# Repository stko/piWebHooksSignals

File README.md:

# piWebHooksSignals & PiPowerOff
## Introduction

This application do two things
- the hardware provides a complete power on/off system, where the raspi can be powered by a battery powerpack and turns himself off after finishing his job. In off state the battery is completely disconnected, so there's no quiescent current which could drain the battery.
 - the software deamon  manages the LEDs and the poweroff. It's controlled by ascii commands received on port 3000.

## Details
The hardware power on is triggered by a short press on the button. When the raspi is going into power off state at the end, it pulls GPIO pin 22 to HIGH, which switches the hardware power off again. (In case of emergency, a longer press also switches the power off)
The sample application reads the `webhooks.cfg` and tries to fire all found webhooks out of the config, while it send ASCII status commands via TCP port 3000 to the LED & power control task. At the end the command EXIT makes the system to power off.

## Install

To install piWebHooksSignals, get a virgin raspian lite image from raspberry.org (tested on raspian stretch)
boot the virgin raspian image, login
start the install script with

    bash <(curl -s https://raw.githubusercontent.com/stko/piWebHooksSignals/master/install.sh)

the installation will take appr. 20 minutes.

After the installation you should adjust your settings before reboot, because after that your file system will be read only (which you can temporarily change with `sudo mount -o remount,rw /` then)

In case of the sample application, the settings would be the UMTS stick settings in `/etc/wvdial.conf` and the web hooks to call in `/etc/piWebHooksSignals/webhooks.cfg`

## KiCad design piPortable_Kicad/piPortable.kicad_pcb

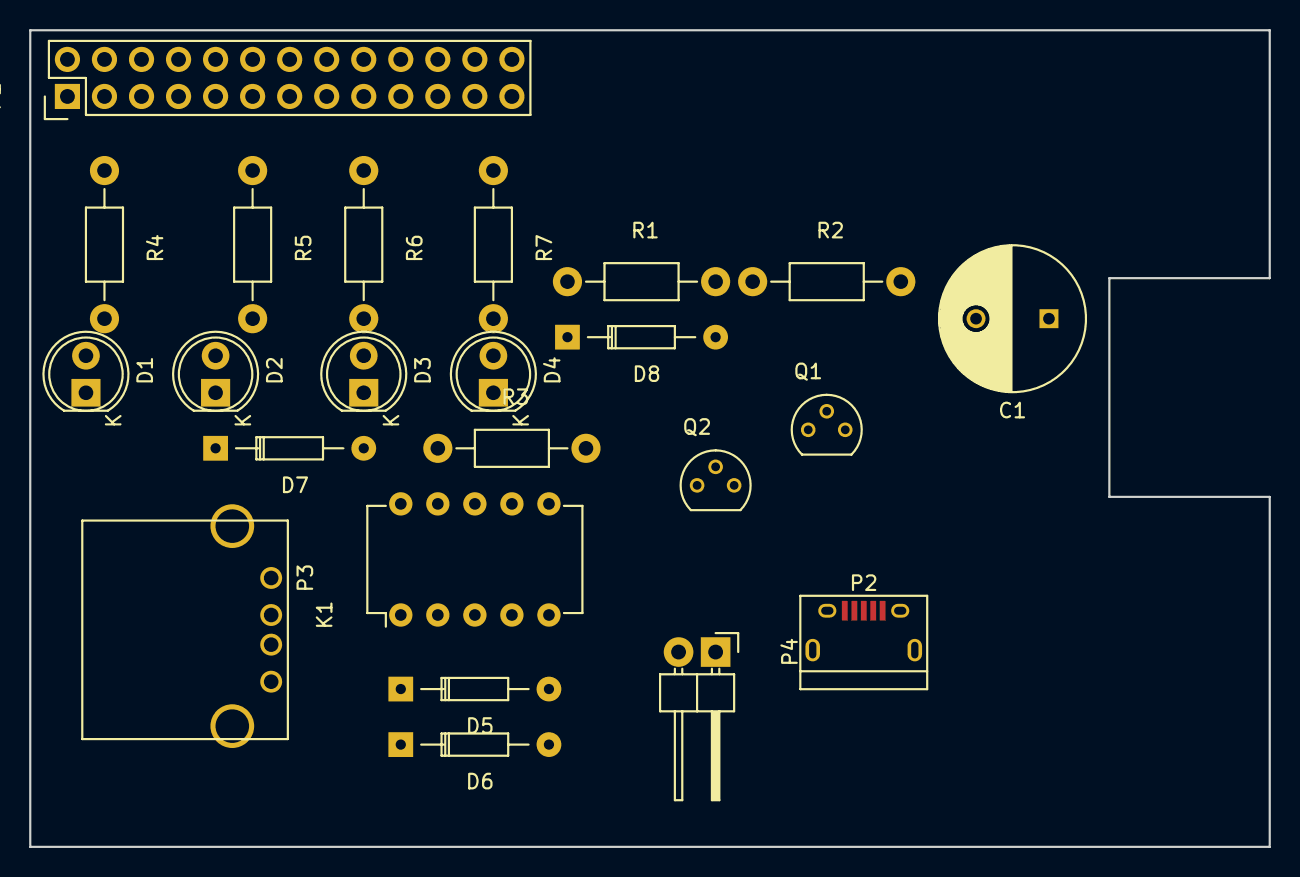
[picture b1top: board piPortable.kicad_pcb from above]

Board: 2 copper layers, 85.0 x 56.0 mm, 23 parts (0 on the bottom side), 17 nets, no tracks yet.

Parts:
C1: CP_Small; C_Radial_D10_L13_P5
D1: Power; LED-5MM
D2: Green; LED-5MM
D3: Yellow; LED-5MM
D4: Red; LED-5MM
D5, D6, D7, D8: D4148; Diode_DO-35_SOD27_Horizontal_RM10
K1: G6S-2; DIP-10_W7.62mm
P1: CONN_13X2; Pin_Header_Straight_2x13
P2: USB_OTG; USB_Micro-B
P3: USB_A
P4: CONN_02X01; Pin_Header_Angled_1x02
Q1, Q2: BC237; TO-92_Molded_Narrow
R1: 1M; Resistor_Horizontal_RM10mm
R2: 10M; Resistor_Horizontal_RM10mm
R3: 10K; Resistor_Horizontal_RM10mm
R4, R5, R6, R7: 330R; Resistor_Horizontal_RM10mm

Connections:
/GPIO17: P1.11, R5.1
/GPIO18: D8.2, P1.12
/GPIO21: P1.13, R6.1
/GPIO22: P1.15, R7.1
GND: C1.2, D1.1, D2.1, D3.1, D4.1, P1.6, P2.5, P2.6, P3.4, P3.5, Q1.3, Q2.3, R2.2
unnamed: C1.1, Q1.2, R1.2, R2.1
unnamed: D1.2, R4.2
unnamed: D2.2, R5.2
unnamed: D3.2, R6.2
unnamed: D4.2, R7.2
unnamed: D5.1, D6.1, K1.1, R3.1
unnamed: D5.2, K1.5, P3.1, R4.1
unnamed: D6.2, D7.2, P4.2
unnamed: D7.1, D8.1, R1.1
unnamed: K1.4, P2.1, P4.1
unnamed: K1.10, Q2.1
unnamed: Q1.1, Q2.2, R3.2

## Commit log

2018-06-10 some tweaks
2018-06-10 working on to make it work...
2018-06-17 some more finetunings
2018-06-30 setup now without unison filesystem, seems to solve poweroff failure
2018-06-30 V1.0
2018-06-30 V1.0 correct a typo
